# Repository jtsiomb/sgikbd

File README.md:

SGI - PS/2 keyboard and mouse converter
=======================================

About
-----
This project is a converter for connecting PS/2 keyboards and mice to old
Silicon Graphics computers which had a proprietary keyboard/mouse interface. It
should work on every non-PS/2 SGI computer with mini-DIN6, DB9 and DB15
keyboard/mouse connectors, such as:

  - Iris 4D series
  - Onyx
  - Indigo

This converter is not necessary, and will not work, for any later SGI machines,
like the indy, O2, indigo2, Octane, and so on, because they use PS/2 keyboards
and mice directly.

It's based on an AVR atmega328pb microcontroller, which reads the PS/2
keyboard and mouse ports, and translates scancodes and events to the protocol
and electrical signalling used by the SGI computers. For details on the
SGI signalling and protocols, see the copy of the keyboard and mouse manpages
from the section 7 of the IRIX manual, under `doc/`.

Directory structure:

  - `hw` - hardware: kicad files and pdf schematics.
  - `fw` - firmware for the AVR microcontroller.
  - `case` - 3D printable enclosure for the sgikbd board.
  - `doc` - relevant documentation.

This repository only contains source files. For schematics in PDF format,
zipped gerbers for PCB manufacturing, and human-readable bill of materials, as
well as detailed build instructions, visit the project website:
http://nuclear.mutantstargoat.com/hw/sgikbd

Alternatively download the latest release archive from:
https://github.com/jtsiomb/sgikbd/releases

The firmware is based on my previous
[a500kbd](https://github.com/jtsiomb/a500kbd) project, so if you see any
leftover references to the Amiga anywhere don't be confused.

Note: rev3 of the sgikbd board uses a jumper (J2) to select the negative supply
voltage source. Make sure to **install a jumper there, do not leave it open**.
In most cases the jumper should be placed in the "default" position, but for
some workstations (notably the R3000 indigo) which don't provide a negative
supply on the keyb/mouse port, you might have to move it to the "R3k indigo"
position instead.

For previous revisions of sgikbd, see
[these instructions](http://nuclear.mutantstargoat.com/hw/sgikbd/indigo_r3000_hack.html)
on how to hack it to work with the R3000 indigo.

License
-------
Copyright (C) 2017-2025 John Tsiombikas <nuclear@mutantstargoat.com>

You are free to use, reproduce, modify, and redistribute any part of this
project, provided you make any derivative work you release, freely available
under the same terms.

Both hardware designs, and software parts of this project, are released under
the terms of the GNU General Public License v3, or at your option any later
version published by the Free Software Foundation. See `LICENSE` for details.

To comply with the license, when releasing derivative hardware designs, you must
provide the full EDA project files, and of course firmware/software source code.
Releasing only images of schematics, gerbers, and firmware binaries is *not*
sufficient for compliance.

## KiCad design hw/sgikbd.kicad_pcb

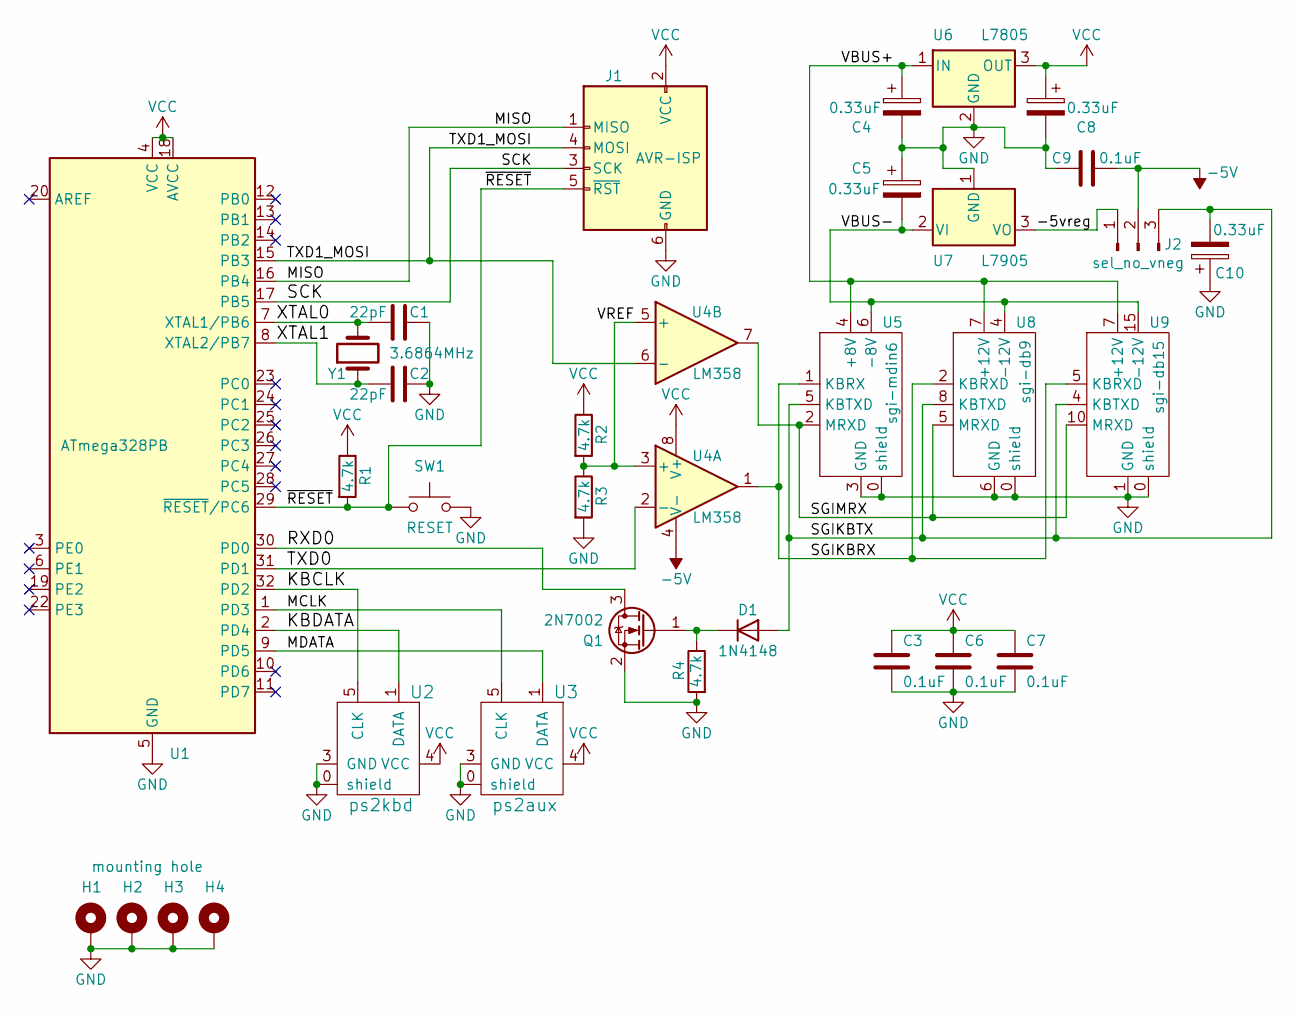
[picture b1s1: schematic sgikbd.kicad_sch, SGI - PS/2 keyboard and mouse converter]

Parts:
C1, C2: 22pF; C_0805_2012Metric_Pad1.18x1.45mm_HandSolder
C3, C6, C7, C9: 0.1uF; C_0805_2012Metric_Pad1.18x1.45mm_HandSolder
C4, C5, C8, C10: 0.33uF; CP_Elec_4x5.4
D1: 1N4148; D_SOD-123
H1, H2, H3, H4: mounting hole; MountingHole_3.2mm_M3_Pad
J1: AVR-ISP; IDC-Header_2x03_P2.54mm_Vertical
J2: sel_no_vneg; PinHeader_1x03_P2.54mm_Vertical
Q1: 2N7002; SOT-23
R1, R2, R3, R4: 4.7k; R_0805_2012Metric_Pad1.20x1.40mm_HandSolder
SW1: RESET; SW_Push_1P1T_NO_6x6mm_H9.5mm
U1: ATmega328PB; TQFP-32_7x7mm_P0.8mm
U2: ps2kbd; minidin6
U3: ps2aux; minidin6
U4: LM358; SOIC-8_3.9x4.9mm_P1.27mm
U5: sgi-mdin6; minidin6
U6: L7805; TO-252-3_TabPin2
U7: L7905; SOT-89-3_Handsoldering
U8: sgi-db9; DSUB-9_Female_Horizontal_P2.77x2.84mm_EdgePinOffset7.70mm_H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
U9: sgi-db15; DSUB-15_Female_Horizontal_P2.77x2.84mm_EdgePinOffset7.70mm_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
Y1: 3.6864MHz; Crystal_SMD_HC49-SD

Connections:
-5V: C9.2, J2.2, U4.4 (V-)
/-5vreg: J2.1, U7.3 (VO)
/KBCLK: U1.32 (PD2), U2.5 (CLK)
/KBDATA: U1.2 (PD4), U2.1 (DATA)
/MCLK: U1.1 (PD3), U3.5 (CLK)
/MDATA: U1.9 (PD5), U3.1 (DATA)
/MISO: J1.1 (MISO), U1.16 (PB4)
/RXD0: Q1.3 (D), U1.30 (PD0)
/SCK: J1.3 (SCK), U1.17 (PB5)
/SGIKBRX: U4.1, U5.1 (KBRX), U8.2 (KBRXD), U9.5 (KBRXD)
/SGIKBTX: C10.2, D1.2 (A), J2.3, U5.5 (KBTXD), U8.8 (KBTXD), U9.4 (KBTXD)
/SGIMRX: U4.7, U5.2 (MRXD), U8.5 (MRXD), U9.10 (MRXD)
/TXD0: U1.31 (PD1), U4.2 (-)
/TXD1_MOSI: J1.4 (MOSI), U1.15 (PB3), U4.6 (-)
/VBUS+: C4.1, U5.4 (+8V), U6.1 (IN), U8.7 (+12V), U9.7 (+12V), U9.8 (+12V), U9.9 (+12V)
/VBUS-: C5.2, U5.6 (-8V), U7.2 (VI), U8.4 (-12V), U9.15 (-12V)
/VREF: R2.2, R3.1, U4.3 (+), U4.5 (+)
/XTAL0: C1.1, U1.7 (XTAL1/PB6), Y1.2
/XTAL1: C2.1, U1.8 (XTAL2/PB7), Y1.1
/~RESET: J1.5 (~RST), R1.2, SW1.1, U1.29 (~RESET/PC6)
GND: C1.2, C2.2, C3.2, C4.2, C5.1, C6.2, C7.2, C8.2, C9.1, C10.1, H1.1, H2.1, H3.1, H4.1, J1.6 (GND), Q1.2 (S), R3.2, R4.2, SW1.2, U1.5 (GND), U1.21 (GND), U2.0 (shield), U2.3 (GND), U3.0 (shield), U3.3 (GND), U5.0 (shield), U5.3 (GND), U6.2 (GND), U7.1 (GND), U8.0 (shield), U8.6 (GND), U8.9 (GND), U9.0 (shield), U9.1 (GND), U9.2 (GND), U9.3 (GND)
unnamed: D1.1 (K), Q1.1 (G), R4.1
VCC: C3.1, C6.1, C7.1, C8.1, J1.2 (VCC), R1.1, R2.1, U1.4 (VCC), U1.18 (AVCC), U2.4 (VCC), U3.4 (VCC), U4.8 (V+), U6.3 (OUT)

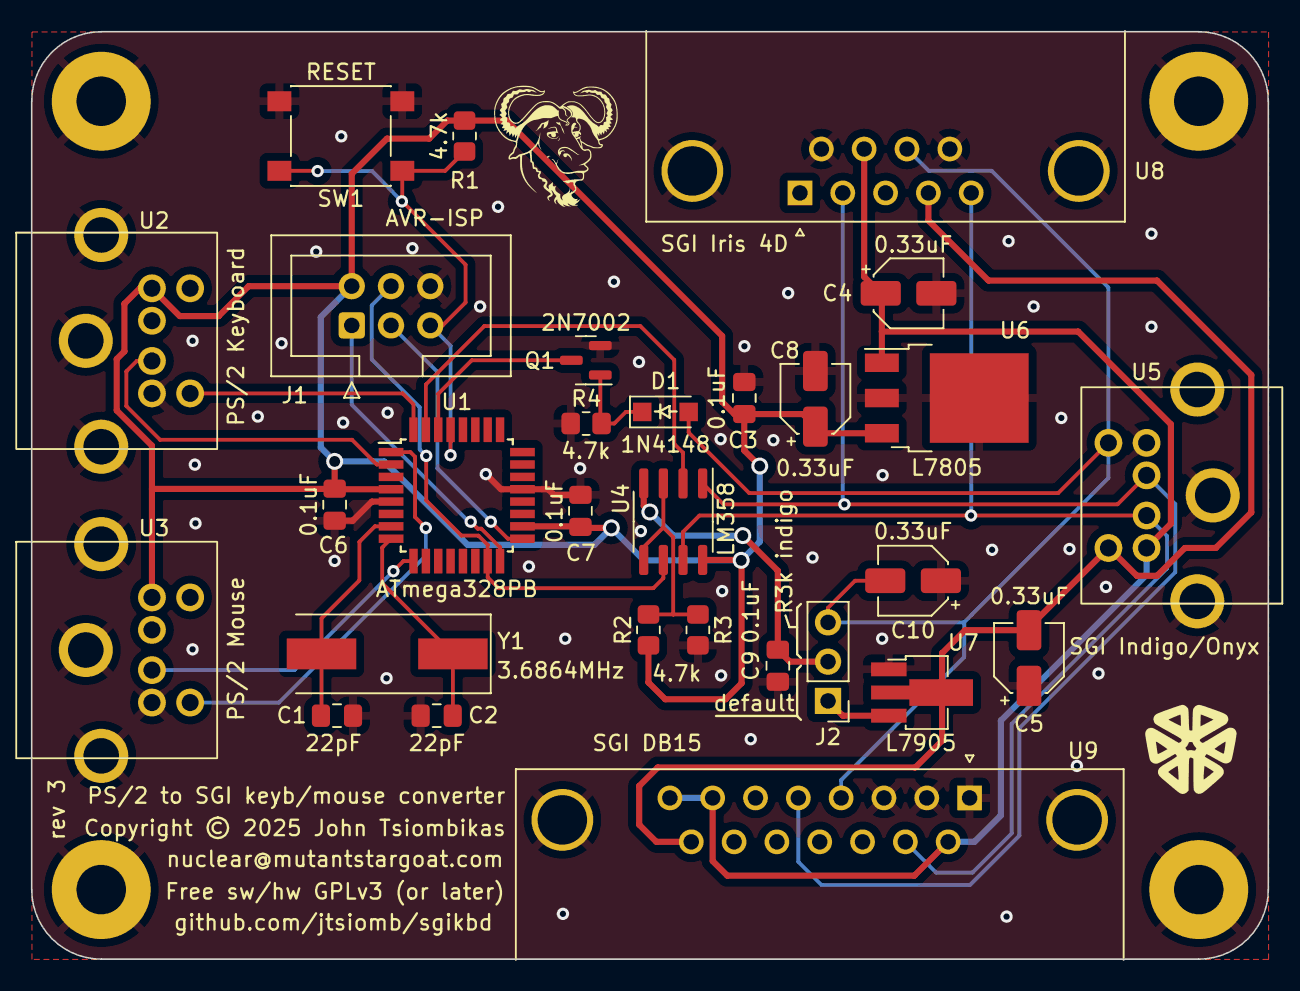
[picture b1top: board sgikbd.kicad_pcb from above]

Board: 2 copper layers, 80.0 x 60.0 mm, 33 parts (0 on the bottom side), 23 nets.

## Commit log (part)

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2022-06-30 sgikbd initial commit (based on a500kbd: https://github.com/jtsiomb/a500kbd)
2022-07-03 migrated the kicad project
2022-07-17 schematic progress
2022-07-18 first board revision completed
2022-07-20 PCB design done + bom and readme
2022-07-27 started on the firmware
2022-07-29 firmware
2022-07-31 - add pull-up to the serial RX pin to go with the transistor inverter bodge - forgot to reset keyflags after processing an extended or break scancode
2022-07-31 fixed UART polarity
2022-08-01 start on the mouse code
2022-08-03 adding PS/2 mouse handling, factoring out common PS/2 code where possible
2022-08-03 first mouse test unsuccessfull, broke keyboard too
2022-08-05 minor schematic cleanup
2022-08-05 fixed mouse handling
2022-08-05 minor readme update
2022-08-06 enable pull-ups on the PS/2 lines
2022-08-09 handle LEDs
2022-08-09 fixed mistranslation of the scancode for the quote key
2022-08-10 update BOM
2022-08-10 readme
2022-08-14 detect printscr, and fixed mapping of numpad 8
2022-08-19 added 3d printed case
2022-08-19 case readme
2024-02-12 added link to the R3000 hack in the readme
2024-02-12 minor README formatting fix
2024-05-01 Updated vector name
2024-05-01 Ignore other values while waiting for mouse ACK
    Some mice seem to send other values before we get the ACK. This was causing auxstate to be reset and the code was back to auxstate=0, waiting for 0xAA which will never happen.
    This change is to ignore other values and stay in auxstate=2 indefinitely until we get the ACK, which eventually comes.
    This makes the Logitech M-S69 mouse work (and possibly others).
2024-06-23 updated kicad files for kicad 8.0
2025-03-17 rev3: jumper-selectable R3K hack
2025-03-27 prepare for release 1.2
2025-03-27 update bom for rev3

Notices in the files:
hw/sgikbd.kicad_pcb:
Copyright © 2025 John Tsiombikas
Free sw/hw GPLv3 (or later)
hw/sgikbd.kicad_sch:
GNU General Public License v3 (or later).
